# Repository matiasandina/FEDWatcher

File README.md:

# FEDWatcher

FEDWatcher is sofware to connect up to 4 [FED3 feeder devices](https://github.com/KravitzLabDevices/FED3/) to one Raspberry Pi 4. 
The Raspberry Pi communicates with the FED3 devices using software serial from the BNC/headphone jack port of the Adafruit feather into the activated UART channels on the Pi.

This repository contains:

* Python code that uses standard Raspberry Pi software and Python packages. 
* The modified software serial library used on the FED3 devices. See [softwareSerial](https://github.com/matiasandina/FEDWatcher/tree/main/softwareSerial).
* Files to print the PCB we are using as a Raspberry Pi HAT for easier interface with the Raspberry Pi 4 pinout. 
* Python code for FEDWatcher GUI, which provides a way for the user to create projects and trigger FEDWatcher easily (see pic below).

## Installation

If you already have an OS installed in your Rasberry Pi, [jump here](#edit-config). Otherwise continue reading.

To set up the Raspberry Pi, begin with flashing a standard image of Raspbian to an SD card. The project was coded and tested using Raspbian Lite with a Gnome Desktop and Raspbian Lite Buster, but any version of Raspbian should work.

For installing the operating system, the official Raspberry Pi Imager can be used. If you would like to install the Gnome desktop, the install will require that you have at least an 8GB SD card, the Pi plugged directly into a monitor, and a wifi or ethernet connection. 

### Gnome desktop

To use the Gnome desktop, first run

```
sudo raspi-config
```

Go into advanced options, select GL driver, install necessary packages if asked, and set the driver to fake KMS. Next, go back into advanced options and make sure you expand filesystem, as this is a large download. Then, back in bash, run

```
git clone https://github.com/TerraGitHuB/gnomeforpi.git && cd gnomeforpi && sudo bash gnomeforpi-install
```

This will take a long time. When the install is finished, the Raspberry Pi will reboot and you will be able to log into the Gnome desktop. In addition, the wifi will be disconnected, but you will be able to reconnect after logging in. After choosing your user and before entering your password, click the settings cog wheel under the password entry box and choose "Gnome for Xorg".

## Edit config

Next, you must enable the four hardware UARTs within the Raspberry Pi. Navigate to `/boot/` and edit `config.txt` however you prefer. This is an example using `nano`

```
sudo nano /boot/config.txt
``` 

> [!TIP]
> In newer versions, `config.txt` has been moved to `/boot/firmware/config.txt`. but everything else applies 

At the end of the file, add on the following statements:

[spi0=on]
# Settings when SPI0 is enabled: no uart4
# No need to repeat uart2, uart3, uart5 if they are always loaded

[spi0=off]
# Settings when SPI0 is disabled: include uart4
dtoverlay=uart4

[all]

dtoverlay=w1-gpio
enable_uart=1
force_eeprom_read=0
disable_poe_fan=1
dtoverlay=uart2
dtoverlay=uart3
dtoverlay=uart5

```

The first two lines disable the GPIO 0 and 1 functionality to be used for uart2. 

You can always remove/comment the first 3 lines above if you need to use a POE fan with the Pi at the same time, but it might create some unexpected erros. Please only do this if you are experienced with this type of config. 

The general mapping to. As of now, FEDWatcher only uses RX ports, but the TX pins will be reserved too.
Below there's mapping between `uartx` -> `GPIOx` -> `board pin #`

```
uart    GPIO                Board Pins (function)
--------------------------------------------------
        TXD RXD CTS RTS     
uart0   14  15              8   10
uart1   14  15              8   10
uart2   0   1   2   3       27  28  (I2C)
uart3   4   5   6   7       7   29
uart4   8   9   10  11      24  21  (SPI0)
uart5   12  13  14  15      32  33  (gpio-fan)
```

You can also check the (UART pinouts here)[https://pinout.xyz/pinout/uart].

This configuration should work when connecting FEDs directly using jumper wires or when using the HAT we designed (see further below).

> [!IMPORTANT]  
> Selecting proper pinout is key to correct functioning of the device. In general, FEDWatcher is flexible and works well with many HATs, but knowledge of the free/used pins is paramount for correct functionality.

Now, you will be able to clone the FEDWatcher github repository into your project and use the functions within it to run your own programs.

## fedwatcher python

To install the software itself, you are advised to use a virtual environment. Clone the repository and then install package requirements in the virtual environment. Installation in Raspberry Pi takes a long time, use the piwheel link in `pip3 install` to make it faster. 

Using conda:

```
git clone https://github.com/matiasandina/FEDWatcher.git
cd FEDWatcher
# tested on python 3.7.3 and 3.10
conda create -n fw_env python==3.10 pip
conda activate fw_env
pip3 install -r requirements.txt --extra-index-url https://www.piwheels.org/simple
```

Using venv (please make sure you get a python version that is compatible!): 

```
git clone https://github.com/matiasandina/FEDWatcher.git
cd FEDWatcher
python3 -m venv fedwatcher 
source fedwatcher/bin/activate
pip3 install -r requirements.txt --extra-index-url https://www.piwheels.org/simple
```

To launch the GUI.

```
cd FEDWatcher/
source fedwatcher/bin/activate
python3 fedwatcher/GUI.py
```

### Desktop entry

You can create a `FEDWatcher.desktop` file in the `Desktop` folder (e.g,. `nano /home/pi/Desktop/FEDWatcher.desktop`). The `Exec` will vary depending on how you installed FEDWatcher. Below, we reproduce an example compatible with the manual way and no virtual environment. 

```
[Desktop Entry]
Type=Application
Comment=FEDWatcher
Name=FEDWatchar
Exec=python3 /home/pi/FEDWatcher/fedwatcher/GUI.py
Icon=/home/pi/FEDWatcher/fedwatcher/img/64.png
Terminal=true
Categories=Utility
StartupNotify=true
```

---
## Hardware

FED3 needs `.ino` sketches to be flashed into it. There are a few things that are crucial for fedwatcher to work properly in FED3 devices.

### Arduino side

On the Arduino side of things, you should have a few modifications to your sketch

Use

```
#include "FED3.h"
```
This will make use of a local `FED3.h` file, instead of the installed FED3 library. We are currently trying to work out a way to merge FEDWatcher into the common FED3 library but for the time being you will need to use a local file.

Use `setSerial(true)` to enable FEDWatcher.

```
void setup() {
  fed3.begin();                                         //Setup the FED3 hardware
  fed3.DisplayPokes = false;                            //Customize the DisplayPokes option to 'false' to not display the poke indicators
  fed3.timeout = 3; //Set a timeout period (in seconds) after each pellet is taken
  
  // Turn to true if you are using FEDWatcher
  fed3.setSerial(true);
}
```

You can check the `sampleSketch` folder which has a free feeding example with 3 second inter trial interval (time between pellets).

### Pinout

To connect the FED3 devices to the Raspberry Pi, you will need a cable that takes the BNC female from the FED3 (old version) or a 3.5 mm male jack to fit the 3.5 mm female jack (new version) and ends to interface with the Raspberry Pi (see below). 

We have made custom cable using awg22 cable, BNC adapters, and male 3.5 mm jacks (see links below). If you are using the newer version of the FED3, any commercial stereo cable will work just fine.

For this program, up to four FED3 devices can be hooked up to a single Raspberry Pi. There are four activated UART ports with receivers at GPIO pins 1, 5, 9, and 13, corresponding to port1, port2, port3, port 4, in order. The unused send pins are located at 0, 4, 8, and 12. **These pins cannot be used while this program is running**. However, if not all ports are used, they can be disabled in the setup function. 

For this setup, the red/hot wire will go to one of the receiver post listed above, and the black/ground wire will go to any ground pin on the Raspberry Pi.

For more information on the pinout of the Raspberry pi visit the [Official Raspberry Documentation](https://www.raspberrypi.org/documentation/usage/gpio/). See below the official pinout for the Raspberry from the docs.

### Design of FEDWatcher HAT

We have also designed a little PCB board that sits on top of the RPi, so that it is easier for users to get started. This board was designed using KiCad 5.1 and 
relies on the following libraries (for footprints and parts):
- https://componentsearchengine.com/part-view/RASPBERRY%20PI%204B%20%2B%20Samtec%20ESP-120-33-G-D/RASPBERRY-PI

Here's how the PCB looks like

There's a bit of soldering involved, but it makes things cleaner:

* Solder female pins to PCB to match Raspberry Pi's pinout.
* Solder female headphone jacks to PCB
* Solder male pins to match fan female connectors

These is how it looks like in our lab.

The designs live on the [hardware](https://github.com/matiasandina/FEDWatcher/tree/main/hardware/RPi_shield) folder in this repository, where you can also find the bill of materials for the HAT.
There are a few generic parts that we recommend using, but similar parts should work.

* [Heat Sink and Fan](https://www.amazon.com/GeeekPi-Raspberry-Cooling-Aluminum-Heatsink/dp/B07PCMTZHF/ref=sr_1_3?crid=Q8C55QA09LS2&keywords=raspberry+pi+fan+aluminum+heatsink&qid=1659374343&sprefix=raspberry+pi+fan+aluminum+heatsink%2Caps%2C65&sr=8-3)
* [BNC adapter](https://www.amazon.com/Connector-Coaxial-Terminal-Adpater-Surveillance/dp/B091Z1V55J/ref=sr_1_22_sspa?crid=16I3NQ8L51GTH&keywords=bnc+adapter+wire&qid=1659374513&sprefix=bnc+adapters+wire,aps,61&sr=8-22-spons&psc=1)
* [M2.5 brass standoff](https://www.amazon.com/HanTof-Raspberry-Standoffs-Standoff-Cylinder/dp/B07KM27KC6/ref=pd_sbs_5/136-6686908-1264224?pd_rd_w=xld4t&pf_rd_p=0f56f70f-21e6-4d11-bb4a-bcdb928a3c5a&pf_rd_r=T61GBPY4VQAJ1AG9K1SB&pd_rd_r=d5b09aac-2d40-4798-8f3f-64e0f1895e47&pd_rd_wg=2Fxwf&pd_rd_i=B07KM27KC6&psc=1)

## Contribute

This is a primary release, please file [issues](https://github.com/matiasandina/FEDWatcher/issues) to contribute to this project.

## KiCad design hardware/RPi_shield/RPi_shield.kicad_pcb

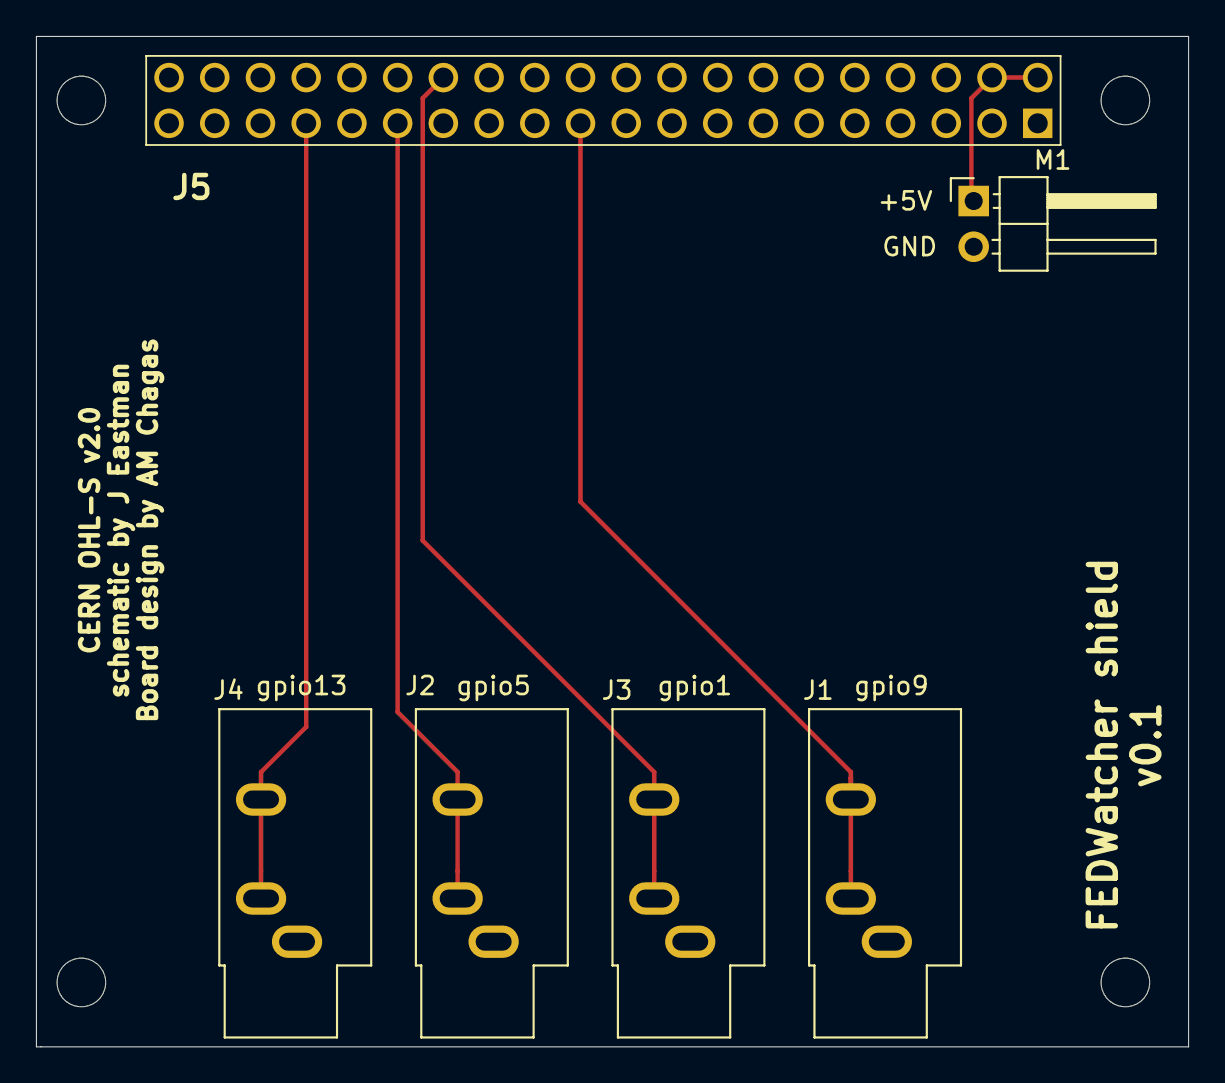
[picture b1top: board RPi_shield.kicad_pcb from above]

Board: 2 copper layers, 64.0 x 56.1 mm, 6 parts (0 on the bottom side), 6 nets.

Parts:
J1, J2, J3, J4: AudioJack3; Jack_3.5mm_CUI_SJ1-3533NG_Horizontal
J5: RASPBERRY_PI_4B_+_Samtec_ESP-120-33-G-D; RASPBERRYPI4B4GB
M1: Fan; PinHeader_1x02_P2.54mm_Horizontal

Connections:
+5V: J5.2, J5.4, M1.1
GND: J1.S, J2.S, J3.S, J4.S, J5.6, J5.9, J5.14, J5.20, J5.25, J5.30, J5.34, J5.39, M1.2
jack1: J3.R, J3.T, J5.28
jack2: J2.R, J2.T, J5.29
jack3: J1.R, J1.T, J5.21
jack4: J4.R, J4.T, J5.33

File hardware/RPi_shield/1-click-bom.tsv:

"References"	"Quantity"	"description"	"manufacturer"	"mpn"	"mouser"
"J1,J2,J3,J4"	4	"Audio Jack 3.5mm 3 pins"	"CUI"	"SJ1-3533NG"	"490-SJ1-3533NG "
"J5"	1	"RASPBERRY_PI_4B_+_Samtec_"	"Samtec"	"ESQ-120-33-G-D"	"200-ESQ12033GD"
"M1"	1	"Fan  connector PinHeader_1x02_P2.54mm"	"Harwin"	"M20-9750242 "	"855-M20-9750242 "

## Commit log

2021-06-21 Added fedwatch and softwareserial code, updated readme
2021-06-22 Made fedwatch.py into a class. Added /boot/config.txt changes to README.md
2021-07-03 Initial commit for object oriented fedwatcher with background process
2021-07-06 Made Fedwatcher object based, runs in background on separate process, fixed multiprocessing
2021-07-07 img in readme not rendering, uploading
2021-07-12 Added dataframes to fedwatcher, implemented saving
2021-07-12 adding sample data for troubleshooting dashboard
2021-07-15 Added skeleton for jam alert handling
2021-07-19 adding horrible GUI
2021-07-21 Example config.yaml, converted pandas dataframe to list of dictionaries, added config file usage, changed save file naming and folder structure
2021-07-23 Implemented more config file checking, changed naming scheme to include session number, added port checking before running
2021-07-23 adding things to GUI, changing filepaths on fedwatcher.py
2021-07-27 improving errors on GUI.py
2021-07-27 adding config session number and saving more data
2021-07-28 Fixed issue with passing configpath, fixed hang on exiting GUI window
2021-07-28 changing exppath to expdir to make it more clear and changing stop button typo
2021-07-28 changing save_dir to expdir to match GUI.py
2021-07-28 doing some changes to make things work
2021-07-28 improving check_input
2021-07-28 aesthetics :smile: :tada:
2021-07-30 added yagmail
2021-07-30 adding minimal email GUI things
2021-07-30 added delete email to fedwatcher.py
2021-07-30 Added email verification when registering email
2021-07-30 adding more email functions
2021-07-30 Fixed error with yagmail error. Added keyring catch exception
2021-07-30 remove keyring storage of password
2021-07-30 modifying GUI.py
2021-08-02 adding nicer GUI :smile:
2021-08-03 Finalized email changes
2021-08-06 fixing load project folder issue
2021-08-09 solving empty entry #22
2021-08-09 adding fedwatcher logo
2021-08-09 changing config to .ini because that's the way configparser actually stores data
2021-08-11 adding logo trial
2021-08-11 adding fedwatcher logos
2021-08-11 implemented exp_end datetime, added new sample data
2021-08-13 solving several issues on GUI.py
2021-08-13 deleting old files
2021-08-13 adding first version.txt file
2021-08-13 changing image location
2021-08-13 adding initial shiny app
2021-11-05 remove weird slashes that make the thing crash
2021-12-13 adding some doc imgs
2021-12-13 adding images to readme
2021-12-13 adding white background to image
2021-12-13 forgot 5v connection
2021-12-17 initial pcb implementation
2021-12-17 save and push work
2021-12-20 modify repo link
2021-12-20 adding camera scriptswithout f(x) yet
2021-12-20 possible solution for formatting issue #28
2021-12-20 finish first iteration of the board and prepare it for kitspace
2021-12-20 add last saves to kicad
2022-01-13 reverse labeling and add logo
2022-01-13 save latest board state
2022-01-13 fix typo on kitspace.yaml file
2022-08-01 adding pics and updating readme
2022-08-12 adding function to sync TDT timestamps in R
2022-08-17 maybe typo fix
2022-08-17 update readme python install
2022-08-19 change numpy requirements, partially solves #36
2022-08-22 adding int conversion to string #36
2022-08-22 adding gitignore
2022-09-05 fixing numpy version again
2023-01-11 adding check for list() events user should try/catch if providing empty list
2023-01-23 updating fedwatcher_tdt with more functions
2023-01-23 changing length for nrow becasue of but
2023-02-16 trying for AMA0
2023-02-16 trying checkbox
2023-02-16 adding telegram basic functionality #5
2023-02-16 fixing typo
2023-02-16 adding some templates for tg function
2023-02-17 update tg info
2023-02-24 adding pics for UART0
2023-03-01 adding tg functionality in both GUI and fedwatcher.py #5
2023-03-02 improving Tg and adding battery info #19
2023-03-02 fix minimal closing bug
2023-05-17 changing notifications back to 6h
2023-05-19 commenting 15 min timeout
2023-05-19 increasing string lengths to prevent corruption #29
2023-05-23 increasing character lengths again to prevent issues #29
2023-05-24 update README #41
2023-06-01 adding explicit type handling, still fighting with consequences of #29
2023-06-01 adding functionality to alert when we raise errors
2023-07-25 fixing variable not present
2023-09-01 updating warning messages
2023-09-15 adding TRE sketches
2023-09-15 fixing if statement
2023-09-26 updating curly braces here
2024-06-05 removing pkg-resources
2024-06-05 venv stuff on reamde
2024-06-05 trying to improve port opening
2024-06-05 imporving prints
2024-06-05 typo
2024-06-05 portpaths
2024-06-05 wrong place
2024-06-06 new gui with port selector
2024-06-06 rename gui.png
2024-06-06 bump!
2024-06-07 use proper order in README.md

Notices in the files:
hardware/RPi_shield/RPi_shield.kicad_pcb:
CERN OHL-S v2.0
